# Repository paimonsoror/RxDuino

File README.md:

RxDuino
=======

The source code for the RxDuino has now entered open source.  For more information please visit the RxDuino website

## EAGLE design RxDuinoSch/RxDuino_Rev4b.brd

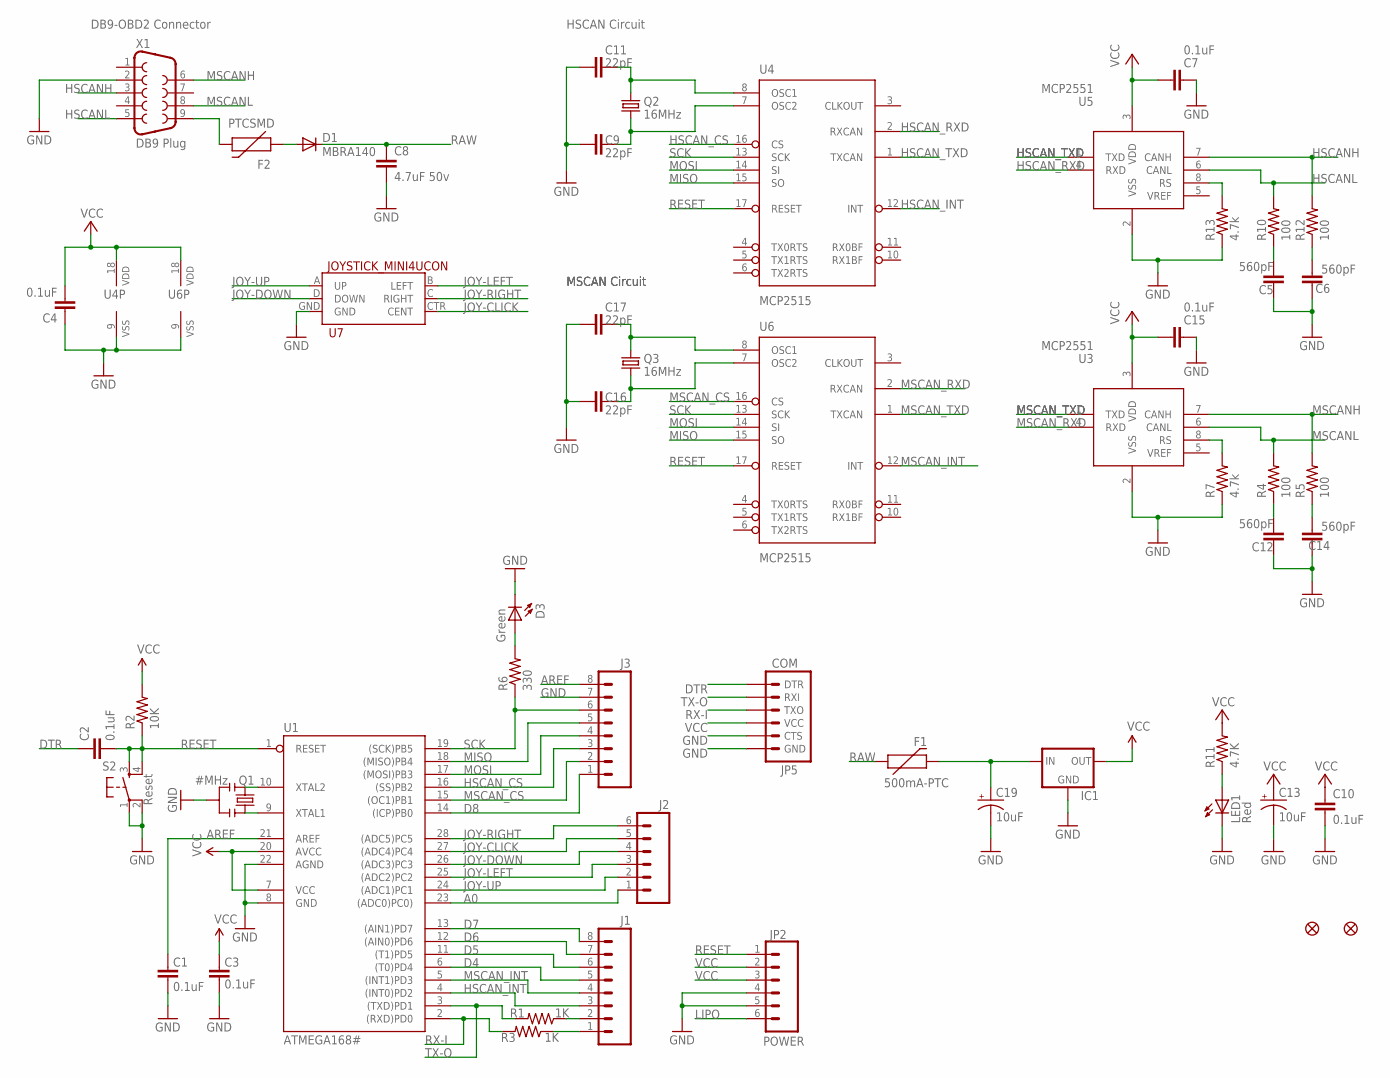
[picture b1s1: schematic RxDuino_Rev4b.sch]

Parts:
C1, C2, C3, C4, C7, C10, C15: 0.1uF; 1206
C5, C6, C12, C14: 560pF; 1206
C8: 4.7uF 50v; 1206
C9, C11, C16, C17: 22pF; 1206
C13, C19: 10uF; PANASONIC_E
D1: MBRA140; SMA-DIODE
D3: Green; LED-1206
F1: 500mA-PTC; PTC-1206
F2: PTCSMD; PTC-1206
IC1: V_REG_78XX-TO-220; TO-220-ALT
J1, J3: M08; 1X08
J2: M06SIP; 1X06
JP2: POWER; 1X06
JP5: COM; 1X06
LED1: Red; LED-1206
Q1: #MHz; RESONATOR-PTH
Q2, Q3: 16MHz; HC49US
R1, R3: 1K; 1206
R2: 10K; 1206
R4, R5, R10, R12: 100; 1206
R6: 330; 1206
R7, R13: 4.7k; 1206
R11: 4.7K; 1206
S2: Reset; TACTILE_SWITCH_SMD
U1: ATMEGA168#; DIL28-3
U3, U5: MCP2551; SO-08M
U4, U6: MCP2515; SO-18W
U7: JOYSTICK_MINI4UCON; JOYSTICK_MINI
U$2, U$4: FIDUCIAL1X2; FIDUCIAL-1X2
X1: DB9 Plug; DB9_MALE

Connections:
A0: J2.1, U1.23 ((ADC0)PC0))
AREF: C1.2, J3.8, U1.21 (AREF)
D1R: D1.A, F2.1
D3N: D3.A, R6.2
D4: J1.5, U1.6 ((T0)PD4)
D5: J1.6, U1.11 ((T1)PD5)
D6: J1.7, U1.12 ((AIN0)PD6)
D7: J1.8, U1.13 ((AIN1)PD7)
D8: J3.1, U1.14 ((ICP)PB0)
DTR: C2.1, JP5.1 (DTR)
GND: C1.1, C3.1, C4.1, C5.1, C6.1, C7.1, C8.2, C9.1, C10.2, C11.1, C12.1, C13.-, C14.1, C15.1, C16.1, C17.1, C19.-, D3.C, IC1.GND, J3.7, JP2.4, JP2.5, JP5.5 (CTS), JP5.6 (GND), LED1.C, Q1.2, R7.1, R13.1, S2.1, S2.2, U1.8 (GND), U1.22 (AGND), U3.2 (VSS), U4.9 (VSS), U5.2 (VSS), U6.9 (VSS), U7.GND, X1.2
HSCANH: R12.2, U5.7 (CANH), X1.3
HSCANL: R10.2, U5.6 (CANL), X1.5
HSCAN_CS: J3.3, U1.16 ((SS)PB2), U4.16 (CS)
HSCAN_INT: J1.3, U1.4 ((INT0)PD2), U4.12 (INT)
HSCAN_RXD: U4.2 (RXCAN), U5.4 (RXD)
HSCAN_TXD: U4.1 (TXCAN), U5.1 (TXD)
HSQ1: C11.2, Q2.2, U4.8 (OSC1)
HSQ2: C9.2, Q2.1, U4.7 (OSC2)
HSRS: R13.2, U5.8 (RS)
JOY-CLICK: J2.5, U1.27 ((ADC4)PC4), U7.CTR (CENT)
JOY-DOWN: J2.4, U1.26 ((ADC3)PC3), U7.D (DOWN)
JOY-LEFT: J2.3, U1.25 ((ADC2)PC2), U7.B (LEFT)
JOY-RIGHT: J2.6, U1.28 ((ADC5)PC5), U7.C (RIGHT)
JOY-UP: J2.2, U1.24 ((ADC1)PC1), U7.A (UP)
LIPO: JP2.6
MEGAP9: Q1.3, U1.9 (XTAL1)
MEGAP10: Q1.1, U1.10 (XTAL2)
MISO: J3.5, U1.18 ((MISO)PB4), U4.15 (SO), U6.15 (SO)
MOSI: J3.4, U1.17 ((MOSI)PB3), U4.14 (SI), U6.14 (SI)
MSCANH: R5.2, U3.7 (CANH), X1.6
MSCANL: R4.2, U3.6 (CANL), X1.8
MSCAN_CS: J3.2, U1.15 ((OC1)PB1), U6.16 (CS)
MSCAN_INT: J1.4, U1.5 ((INT1)PD3), U6.12 (INT)
MSCAN_RXD: U3.4 (RXD), U6.2 (RXCAN)
MSCAN_TXD: U3.1 (TXD), U6.1 (TXCAN)
MSQ1: C17.2, Q3.2, U6.8 (OSC1)
MSQ2: C16.2, Q3.1, U6.7 (OSC2)
MSRS: R7.2, U3.8 (RS)
PTCN: F2.2, X1.9
R4N: C12.2, R4.1
R5N: C14.2, R5.1
R10N: C5.2, R10.1
R11N: LED1.A, R11.1
R12N: C6.2, R12.1
RAW: C8.1, D1.C, F1.1
RAWN: C19.+, F1.2, IC1.IN
RESET: C2.2, JP2.1, R2.1, S2.3, S2.4, U1.1 (RESET), U4.17 (RESET), U6.17 (RESET)
RX-I: JP5.3 (TXO), R3.2, U1.2 ((RXD)PD0)
RX-IP: J1.2, R1.1
SCK: J3.6, R6.1, U1.19 ((SCK)PB5), U4.13 (SCK), U6.13 (SCK)
TX-O: JP5.2 (RXI), R1.2, U1.3 ((TXD)PD1)
TX-OP: J1.1, R3.1
VCC: C3.2, C4.2, C7.2, C10.1, C13.+, C15.2, IC1.OUT, JP2.2, JP2.3, JP5.4 (VCC), R2.2, R11.2, U1.7 (VCC), U1.20 (AVCC), U3.3 (VDD), U4.18 (VDD), U5.3 (VDD), U6.18 (VDD)

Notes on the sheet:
MSCAN Circuit
HSCAN Circuit
DB9-OBD2 Connector

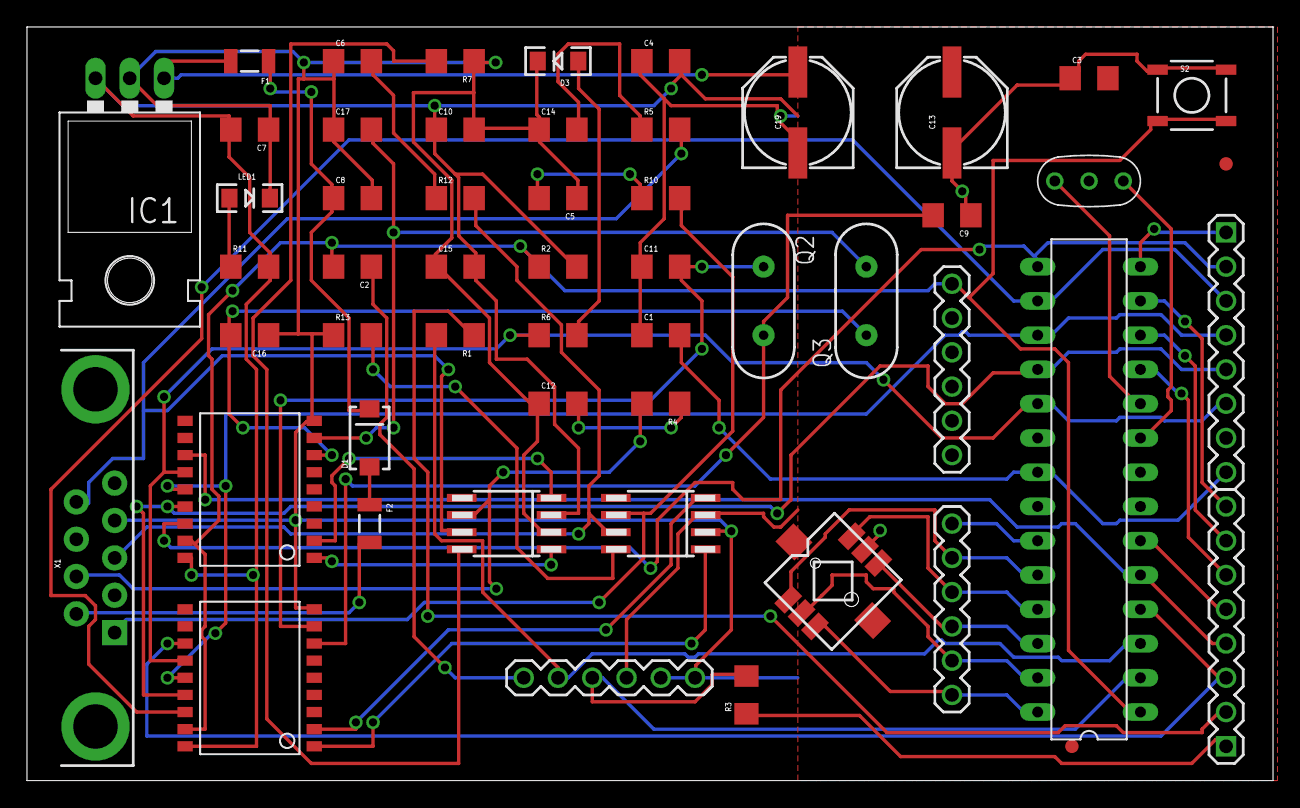
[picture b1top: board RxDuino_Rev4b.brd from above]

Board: 2 copper layers, 92.4 x 55.9 mm, 53 parts (0 on the bottom side), 53 nets.

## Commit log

2013-07-08 Initial Source Commit
2013-07-08 Updated file headers
2013-07-11 Fixed some formatting
